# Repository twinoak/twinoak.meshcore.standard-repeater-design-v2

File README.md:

# TwinOak Standard Repeater Design v2

## General design concept and project goals
The thought behind this project came to life after quite a few failures in OTA firmware updates. There was need for a better, and more stable, way of doing the firmware updates. 
Besides the devices being bricked from the OTA process, repeaters can also sit quite a long distance away, so it would also be desireable to have something that could update remotely, from the comfort of a desk. 
One could consider using LoRa for sending the updates to the repeaters, but since the network is already congested enough, it seems like a bad idea to pile even more load on that band, even assuming that it somehow would be possible to get a stable link to all the repeater sites.

It was decided to go for a design which incorporated an LTE-M module for managinge the node. This gives almost 100% coverage(in Denmark at least!) and high bandwidth for firmware transfers. 
The structure looked something like this:
```mermaid
flowchart LR
    subgraph Mesh plane
    A@{ shape: cloud, label: "Mesh network" } <--> B[LoRa module]
    end
    B[LoRa module] <-.-> C[LTE-M module]
    subgraph Management plane
    C <--> D@{ shape: cloud, label: "Internet" }
    end
```

Besides the problematic management of remote nodes, there is also a few other features to address with this new repeater design. This meant that the primary goals for the project ended up being:
1. <b>Remote management</b>. Being able to do management remotely based on existing LTE infrastructure. Only management, no data via LTE.
2. <b>Superior noise "rejection"</b> with radio in RF shielding and using proper cables and isolation to give the LoRa the best possible noise floor. Previous experience with SenseCAP Solar P1 nodes, even though they are very nice nodes, proved that they are just plastic enclosures with no RF protection. Put them next to a cell tower and you are in trouble! A bit ironic that the biggest nemesis regarding noise in MeshCore repeaters is LTE, when this going to use LTE as the transport for the management plane!
3. <b>Integrated cavity filter</b>. There has been multiple issues with noise in all many locations. There is always a cell tower(or some DAB/DVT/whatever tower) sitting just next to great locations. The Solar P1 only offers the option to add a small SAW filter, but one goal of this project is that it should to be easy to add a good cavity filter. Even maybe be the default.
4. <b>Modularity</b>. Things change fast; firmware, features and other software changes fast! But hardware also changes. With the Solar P1 one would have to replace the entire unit if a new and better radio became available. This project should solve this by enabling changing JUST the radio or JUST the solarpanel or JUST the batteries. Not doing a complete "forklift upgrade" everytime is a must.

## Hardware design principle
The hardware is split into 3 parts:
1. The LoRa part
2. The power part
3. The management part

To make these function together in a modular way each part has been split into multiple "levels" with increasing amount of specialization the higher the level. This has been illustrated here:
```mermaid
block
  columns 7
  block:stuff:2
    columns 1
    A1["LoRa modul"] 
    space
    A2["LoRa adapter board"] 
    space
    A3["Platform board"]
    space
    space
  end
  space
  block:stuff2:2
    columns 1
    space
    space
    space
    space
    B3["Platform mgmt"]
    space
    B4["Power"]
  end
  space
  block:stuff3:2
    columns 1
    C1["LTE modul"] 
    space
    C2["LTE adapter board"]
    space
    C3["Platform board"]
    space
    space
  end

  %% Arrows vertically
  A1 <--> A2
  A2 <--> A3

  B4 --> B3

  C1 <--> C2
  C2 <--> C3

  %% Arrows horisontally
  A3 <--> B3
  B3 <--> C3
```
From the bottom up:
- <b>Power</b> is just that: Simple DC power source from either solarpanel, grid connection or battery.
- <b>Platform</b> and <b>Platform management</b> is introducing management of the power from the power source and handling signaling between the two platform boards. Each platformboard is just supplying simple power to the upper levels and generic IO between the levels.
- <b>Adapters</b> change the generic IO and power from the platform to the specific needs of the module above it. That could be board specific power management, levelshifting of IO signals and routing to the proper pins for the given module above.
- <b>Radio modules</b> is the actual off-the-shelf radio modules, such as a Heltec LoRa module like the T096 or similar.

Each of the 3 parts should be kept as RF isolated as possible as the two radio modules will likely interfer with each other. So the parts also indicate an "physical seperation" with RF shielding. To make this as good as possible the entire repeater should be house inside a RF shielded enclosure and both the LoRa part and the management part should be kept in seperate RF shielded enclosures. Great care should be taken at the interfaces between each part, such that RF noise don't traverse the bounderies between each part.

### Pinouts and inter-board wiring

Every pin of the D-subs, the A↔B ribbon, the platform boards and all adapter mappings is documented in
[`hardware/pcb/INTERCONNECT.md`](hardware/pcb/INTERCONNECT.md) — including the I2C bus plan (LoRa is master,
INA3221 @0x42, RV-3028 @0x52), the LoRa↔Walter UART link, the remote power-kill behaviour and JLCPCB part
references. Update that file first whenever the wiring changes.

## Bill-of-materials and links to sources

| Component            | Brand      | Model                             | Source                                                                                                   | Price     |
|----------------------|------------|-----------------------------------|----------------------------------------------------------------------------------------------------------|----------:|
| <u>*External components*</u>                                                                                                                                                                 |
| Antenna, LoRa        | Vinnant    | CC868/8-PEL 10dBi                 | [Hoeg teknik](https://hoegteknik.dk/shop/da/dv-nodermeshtastic/483-8dbd-58-antenne-for-868-mhz.html)     |   599 DKK |
| Antenna, LTE-M       | SR passives| IP67, N-Male, 5dBi                | [TME](https://www.tme.eu/dk/en/details/5g-ant-rs02w-n/gsm-antennas/sr-passives/)                         |    73 DKK |
| Cable                | Bevotop    | LMR240, N Male to N Male, 80cm    | [Aliexpress](https://www.aliexpress.com/item/1005002640557645.html)                                      |   ~70 DKK |
| Pipe                 |            | 1" pipe, 200cm                    | [Webshop](https://shop.erik-larsen.dk/products/pipe-galv?variant=39625182412883)                         |   150 DKK |
| Brackets             |            | Pipeclamps, set of 2, max 60mm    | [Amazon](https://www.amazon.de/-/da/Premium-mastklemme-dobbeltklemme-galvaniseret-dobbelt/dp/B010UL5B66) |   ~67 DKK |
| Enclosure            |            | Diecast alu box, IP67             | [Aliexpress](https://www.aliexpress.com/item/1005007492347455.html)                                      |  ~185 DKK |
| Solar panel          | Cellevia   | 10W Solar Panel                   | [TME](https://www.tme.eu/dk/en/details/cl-sm10p/photovoltaic-modules/cellevia-power/)                    |    76 DKK |
| Vent valve           |            | M16 watertight alu vent valve     | [Aliexpress](https://www.aliexpress.com/item/1005012242062756.html)                                      |   ~20 DKK |
| Bracket              |            | For solar panel                   | TBD                                                                                                      |           |
| Bracket              |            | For enclosure                     | TBD                                                                                                      |           |
| <u>*Internal components*</u>                                                                                                                                                                 |
| Backplates           | Custom     | Set of 2pce, 1,5mm lasercut alu   | (Fusion link? DXF?)                                                                                      |   280 DKK |
| RF boxes             | Gainta     | G103-IP67, 64x98x34mm, alu, 2pce  | [TME](https://www.tme.eu/dk/en/details/g103-ip67/multipurpose-enclosures/gainta/)                        |   108 DKK |
| Cavity filter        | Sysmocom   | 7Mhz Cavity filter(Link to test?) | [Sysmocom](https://shop.sysmocom.de/868-863..870-MHz-cavity-filter-ISM-LoRa-SigFox-Helium/cf866.5-kt30)  |  ~400 DKK |
| Battery              | Meshnology | 10.000mA LiPo battery             | [Meshnology](https://meshnology.com/collections/frontpage/products/3-7v-10000mah-lipo-battery-with-usb-charger-protection-for-arduino-esp32-drone?variant=46431266963694) | ~150 DKK |
| Battery NTC          | muRata     | NXFT15XH103FEAB050, 10k ±1%, B25/85 3434K, 50 mm leads — must be a B≈3435K part (TS divider R5/R6 on conn-B); a generic B3950 NTC moves the charge window to 3.5…38.6 °C | [LCSC C17314387](https://www.lcsc.com/product-detail/C17314387.html) | ~4 DKK |
| Connector, NTC (J6)  | JST        | PHR-2 housing + 2x SPH-002T-P0.5S contact (24–30 AWG), JST PH 2.0 mm | [LCSC C157955](https://www.lcsc.com/product-detail/C157955.html) / [C111515](https://www.lcsc.com/product-detail/C111515.html) | <1 DKK |
| Connector, battery (J7) | JST     | EHR-2 housing + 2x SEH-001T-P0.6L contact (22–26 AWG, use 22 AWG for the 2 A lead; P0.6 C263767 covers 22–30), JST EH 2.5 mm | [LCSC C161659](https://www.lcsc.com/product-detail/C161659.html) / [C392073](https://www.lcsc.com/product-detail/C392073.html) | <1 DKK |
| Cable                |            | U.FL -> SMA pigtail, 10cm         | [Aliexpress](https://www.aliexpress.com/item/1005009937311685.html)                                      |   ~10 DKK |
| Cable                |            | N-female -> SMA pigtail, 10cm     | [Aliexpress](https://www.aliexpress.com/item/1005008984322302.html)                                      |   ~10 DKK |
| Cable                |            | N-female -> SMA pigtail, 20cm     | [Aliexpress](https://www.aliexpress.com/item/1005008984322302.html)                                      |   ~10 DKK |
| Cable                |            | SMA -> SMA pigtail, 10cm          | [Aliexpress](https://www.aliexpress.com/item/1005006890065800.html)                                      |   ~10 DKK |
| <u>*Radio modules*</u>                                                                                                                                                                       |
| LoRa module          | Heltec     | Heltec V3, ESP32 based            | [Heltec](https://heltec.org/project/wifi-lora-32-v3/)                                                    |  ~120 DKK |
| *...or...*                                                                                                                                                                                   |
| LoRa module          | Heltec     | Heltec T096, nRF52 based          | [Heltec](https://heltec.org/project/t096/)                                                               |  ~230 DKK |
| LTE module           | Quickspot  | Walter LTE MCU, ESP32 based       | [TinyTronics](https://www.tinytronics.nl/nl/development-boards/microcontroller-boards/met-telecommunicatie/walter-esp32-s3-iot-development-board-cat-m-nb-iot-en-gnss-gm02sp) |   ~510 DKK |
| <u>*Custom PCBs*</u>                                                                                                                                                                         |
| Platform board       |            | TBD                               |                                                                                                          |           |
| Heltec V3 adapter    |            | TBD                               |                                                                                                          |           |
| *...or...*                                                                                                                                                                                   |
| Heltec T096 adapter  |            | TBD                               |                                                                                                          |           |
| LoRa connector board |            | TBD                               |                                                                                                          |           |
| LTE connector board  |            | TBD                               |                                                                                                          |           |
| <u>*Electrical components*</u>                                                                                                                                                               |
| D-sub connector      | Amphenol   | FCE17-E09SM-250, 9-pin, filter, x2| [Mouser](https://eu.mouser.com/en/ProductDetail/Amphenol-Commercial-Products/FCE17-E09SM-250)            |  ~175 DKK |
| D-sub connector      | Amphenol   | L717DFE09PT, 9-pin, male PCB, x2  | [Mouser](https://eu.mouser.com/en/ProductDetail/Amphenol-Commercial-Products/L717DFE09PT)                |  ~100 DKK |
| Capacitor            | Panasonic  | 16SEPG470M, 470µF PolyAlu, x1 — or JLC-assemblable Honor Elec RYHT16V470UF8*11 (LCSC C48970577, 8×11.5 mm, 3.5 mm pitch, 14 mΩ, 125 °C) | [TME](https://www.tme.eu/dk/en/details/16sepg470m/tht-polymer-capacitors/panasonic/) / [JLCPCB](https://jlcpcb.com/partdetail/C48970577) |   ~10 DKK |
| Capacitor            | AISHI      | EWH1CM101E11OT, 100µF, x2         | [TME](https://www.tme.eu/dk/en/details/ce-100_16pht-y/tht-electrolytic-capacitors/aishi/ewh1cm101e11ot/) |    ~1 DKK |
| Capacitor            | SR passives| CCT-10N/100V-S, 10nF Ceramic, x2  | [TME](https://www.tme.eu/dk/en/details/cct-10n_100v-s/mlcc-tht-capacitors/sr-passives/ct40805b103k101f1r/) |  ~1 DKK |                                                                                                        |           |
| Connector            |            | Pin headers for radio modules?    | TBD                                                                                                      |           |
| Connector            |            | Low profile headers for adapters? | TBD                                                                                                      |           |

Total: ~3.250DKK + TBD + solder/heatshrink/screws/wires/etc + shipping/customs/fees/etc

## LTE-M providers

### Lebara
Lebara SIM card, their cheapest plan, has been tested and it worked fine with the Walter MCU and could get contact with the internet without issues.

### NexCon
The LTE provider nexcon.io has been tested. They have a 25MB/month plan that is VERY cheap, like 1eur/month per SIM card including a management website that is VERY nice! Can highly recommend them, however they might only serve commercial customers, so check that first.

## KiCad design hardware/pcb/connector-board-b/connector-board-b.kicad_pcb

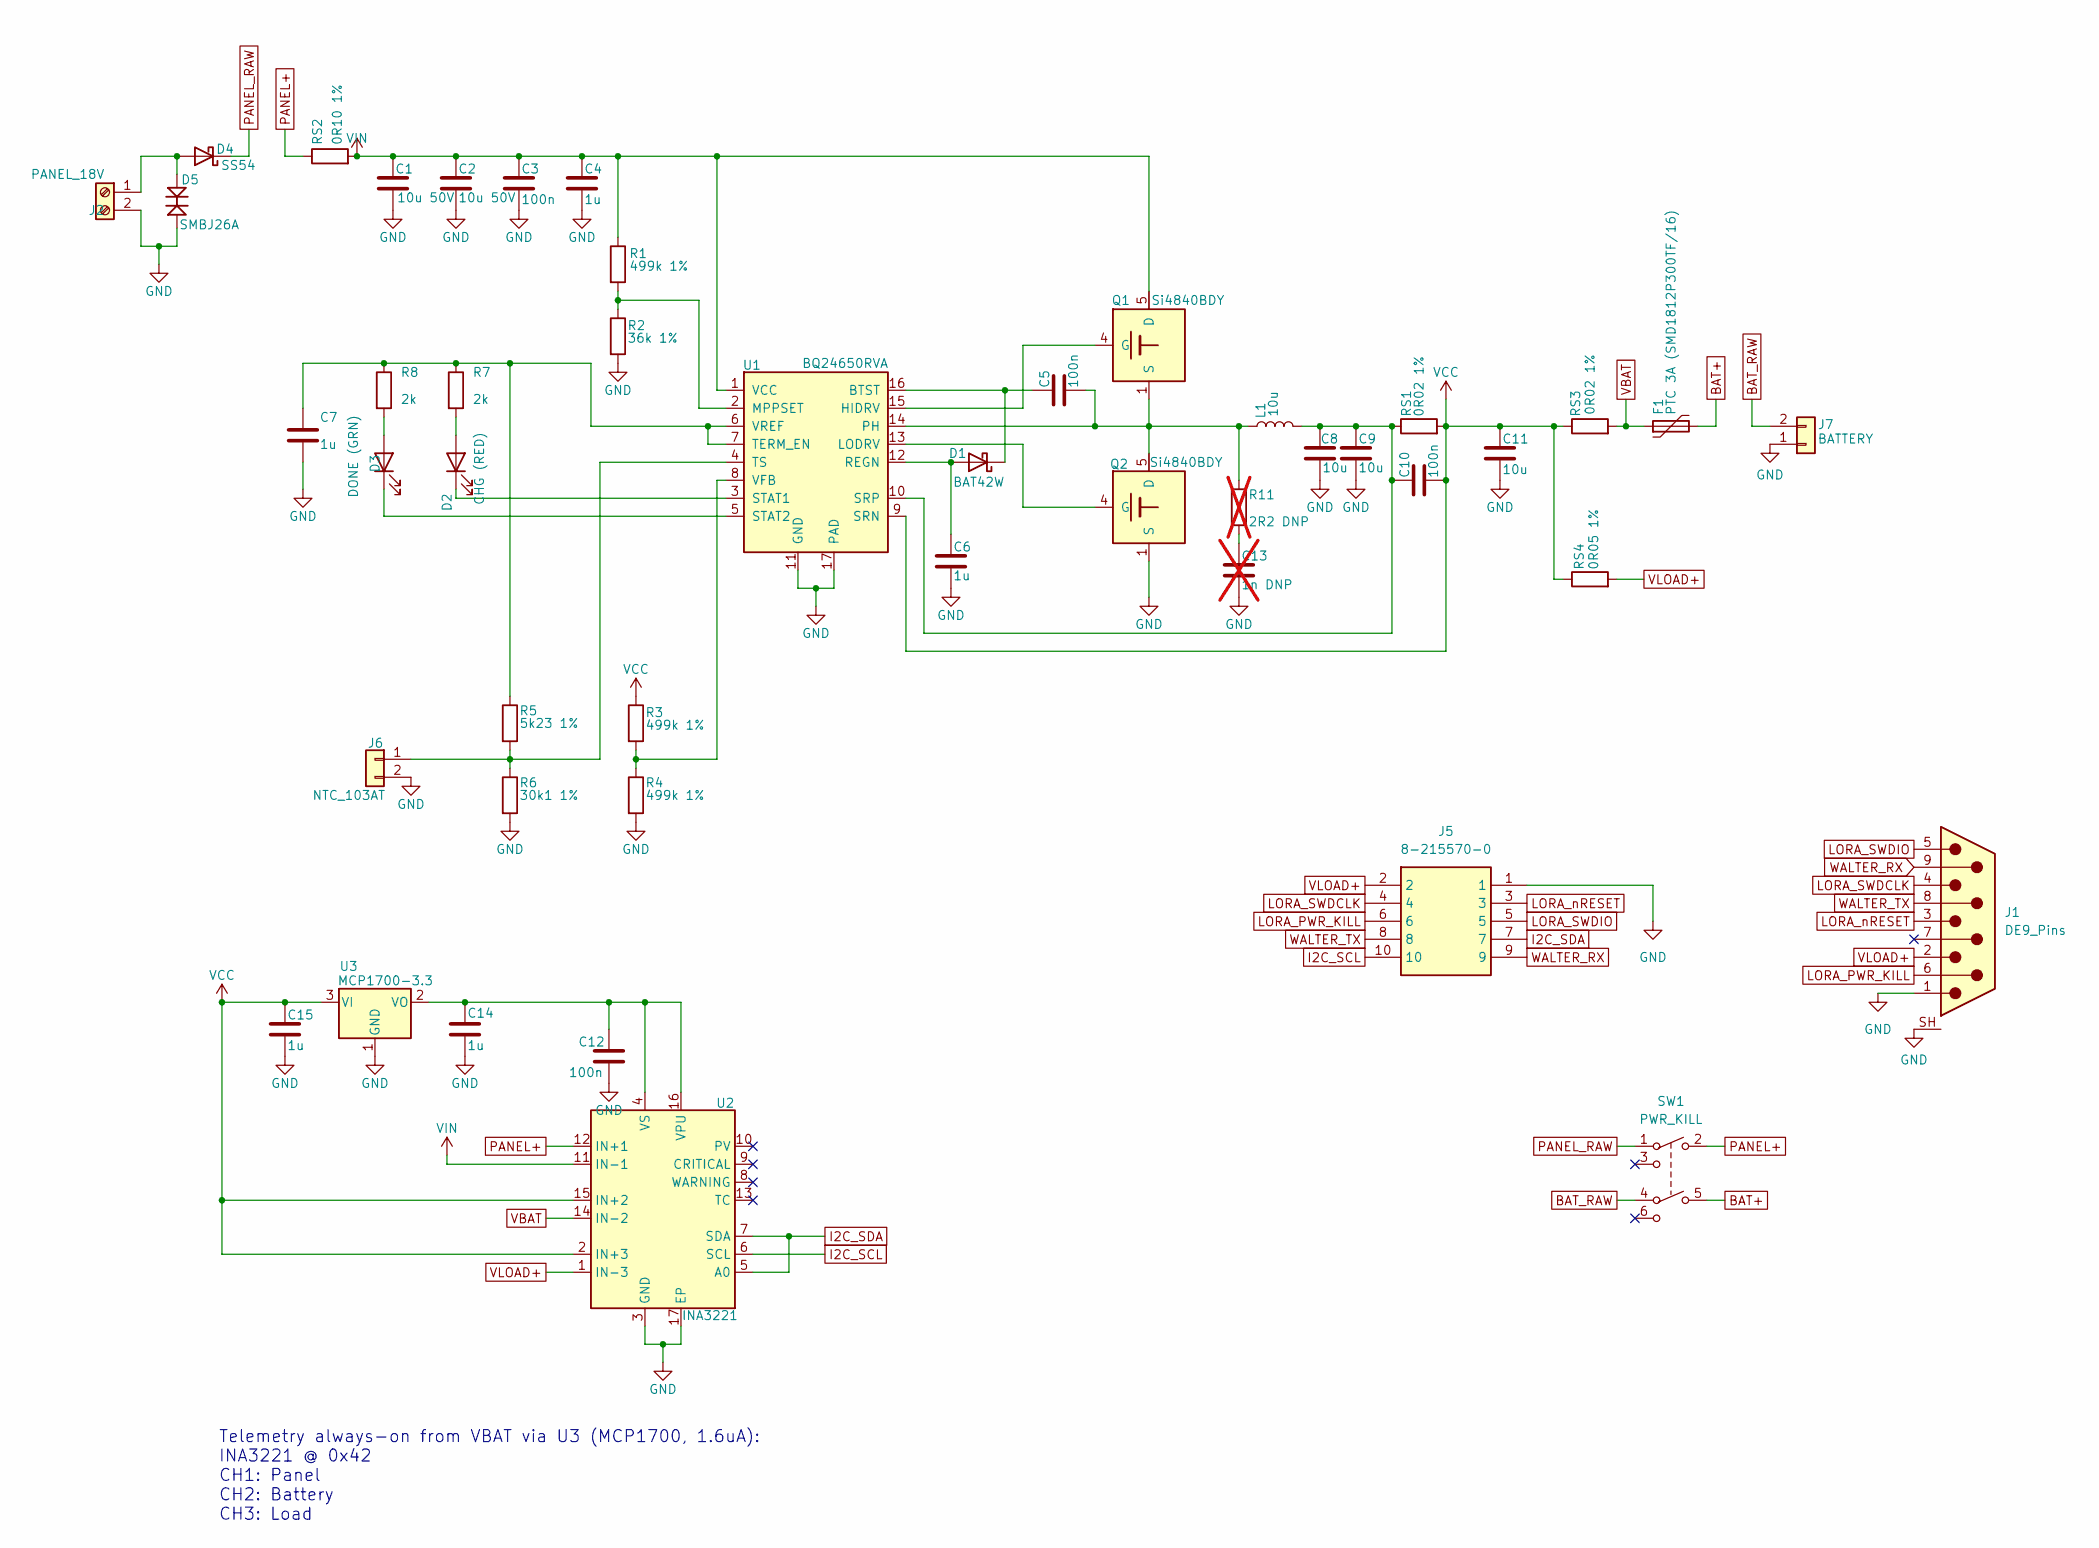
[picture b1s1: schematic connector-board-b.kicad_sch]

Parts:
C1, C2: 10u 50V; C_1210_3225Metric; LCSC Part # C138687
C3, C5, C10, C12: 100n; C_0805_2012Metric; LCSC Part # C49678
C4, C6, C7, C14, C15: 1u; C_0805_2012Metric; LCSC Part # C28323
C8, C9, C11: 10u; C_1206_3216Metric; LCSC Part # C13585
C13: 1n DNP; C_0805_2012Metric; LCSC Part # C94121; not fitted
D1: BAT42W; D_SOD-123; LCSC Part # C134396
D2: CHG (RED); LED_0805_2012Metric; LCSC Part # C84256
D3: DONE (GRN); LED_0805_2012Metric; LCSC Part # C2297
D4: SS54; D_SMA; LCSC Part # C22452
D5: SMBJ26A; D_SMB; LCSC Part # C123820
F1: PTC 3A (SMD1812P300TF/16); Fuse_1812_4532Metric; LCSC Part # C702820
J1: DE9_Pins; DSUB-9_Pins_Vertical_P2.77x2.84mm_MountingHoles
J2: PANEL_18V; TerminalBlock_MaiXu_MX126-5.0-02P_1x02_P5.00mm; LCSC Part # C5188434
J5: 8-215570-0; 82155700; Manufacturer_Part_Number 8-215570-0
J6: NTC_103AT; JST_PH_B2B-PH-K_1x02_P2.00mm_Vertical; LCSC Part # C131337
J7: BATTERY; JST_EH_B2B-EH-A_1x02_P2.50mm_Vertical; LCSC Part # C160262
L1: 10u; L_Vishay_IHLP-4040; LCSC Part # C845066
Q1, Q2: Si4840BDY; SOIC-8_3.9x4.9mm_P1.27mm; LCSC Part # C558269
R1, R3, R4: 499k 1%; R_0805_2012Metric; LCSC Part # C17721
R2: 36k 1%; R_0805_2012Metric; LCSC Part # C4360
R5: 5k23 1%; R_0805_2012Metric; LCSC Part # C17739
R6: 30k1 1%; R_0805_2012Metric; LCSC Part # C21841
R7, R8: 2k; R_0805_2012Metric; LCSC Part # C17604
R11: 2R2 DNP; R_0805_2012Metric; not fitted
RS1, RS3: 0R02 1%; R_1206_3216Metric; LCSC Part # C2903502
RS2: 0R10 1%; R_1206_3216Metric; LCSC Part # C25334
RS4: 0R05 1%; R_1206_3216Metric; LCSC Part # C2904224
SW1: PWR_KILL; SW_Toggle_CAX_MTS202C3D1_RightAngle; LCSC Part # C55159901
U1: BQ24650RVA; Texas_RVA0016A_VQFN-16-1EP_3.5x3.5mm_P0.5mm_EP2.1x2.1mm; LCSC Part # C53712
U2: INA3221; Texas_RGV0016A_VQFN-16-1EP_4x4mm_P0.65mm_EP2.1x2.1mm; LCSC Part # C181255
U3: MCP1700-3.3; SOT-23; LCSC Part # C39051

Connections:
BAT+: F1.2, SW1.5 (COM2)
BAT_RAW: J7.2, SW1.4 (A2)
GND: C1.2, C2.2, C3.2, C4.2, C6.2, C7.2, C8.2, C9.2, C11.2, C12.2, C13.2, C14.2, C15.2, D5.2, J1.1 (1_1), J1.SH, J2.2, J5.1, J6.2, J7.1, Q2.1 (S), Q2.2 (S), Q2.3 (S), R2.2, R4.2, R6.2, U1.11 (GND), U1.17 (PAD), U2.3 (GND), U2.17 (EP), U3.1 (GND)
I2C_SCL: J5.10, U2.6 (SCL)
I2C_SDA: J5.7, U2.5 (A0), U2.7 (SDA)
LORA_PWR_KILL: J1.6 (6_6), J5.6
LORA_SWDCLK: J1.4 (4_4), J5.4
LORA_SWDIO: J1.5 (5_5), J5.5
LORA_nRESET: J1.3 (3_3), J5.3
unnamed: C13.1, R11.2
unnamed: C6.1, D1.2 (A), U1.12 (REGN)
unnamed: C5.1, D1.1 (K), U1.16 (BTST)
unnamed: D2.2 (A), R7.2
unnamed: D2.1 (K), U1.3 (STAT1)
unnamed: D3.2 (A), R8.2
unnamed: D3.1 (K), U1.5 (STAT2)
unnamed: D4.2 (A), D5.1, J2.1
unnamed: J6.1, R5.2, R6.1, U1.4 (TS)
unnamed: Q1.4 (G), U1.15 (HIDRV)
unnamed: Q2.4 (G), U1.13 (LODRV)
unnamed: R1.2, R2.1, U1.2 (MPPSET)
unnamed: C5.2, L1.1, Q1.1 (S), Q1.2 (S), Q1.3 (S), Q2.5 (D), Q2.6 (D), Q2.7 (D), Q2.8 (D), R11.1, U1.14 (PH)
unnamed: C8.1, C9.1, C10.1, L1.2, RS1.1, U1.10 (SRP)
unnamed: C7.1, R5.1, R7.1, R8.1, U1.6 (VREF), U1.7 (TERM_EN)
unnamed: R3.2, R4.1, U1.8 (VFB)
unnamed: C12.1, C14.1, U2.4 (VS), U2.16 (VPU), U3.2 (VO)
PANEL+: RS2.1, SW1.2 (COM1), U2.12 (IN+1)
PANEL_RAW: D4.1 (K), SW1.1 (A1)
VBAT: F1.1, RS3.2, U2.14 (IN-2)
VCC: C10.2, C11.1, C15.1, R3.1, RS1.2, RS3.1, RS4.1, U1.9 (SRN), U2.2 (IN+3), U2.15 (IN+2), U3.3 (VI)
VIN: C1.1, C2.1, C3.1, C4.1, Q1.5 (D), Q1.6 (D), Q1.7 (D), Q1.8 (D), R1.1, RS2.2, U1.1 (VCC), U2.11 (IN-1)
VLOAD+: J1.2 (2_2), J5.2, RS4.2, U2.1 (IN-3)
WALTER_RX: J1.9 (9_9), J5.9
WALTER_TX: J1.8 (8_8), J5.8

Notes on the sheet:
Telemetry always-on from VBAT via U3 (MCP1700, 1.6uA): INA3221 @ 0x42 CH1: Panel CH2: Battery CH3: Load

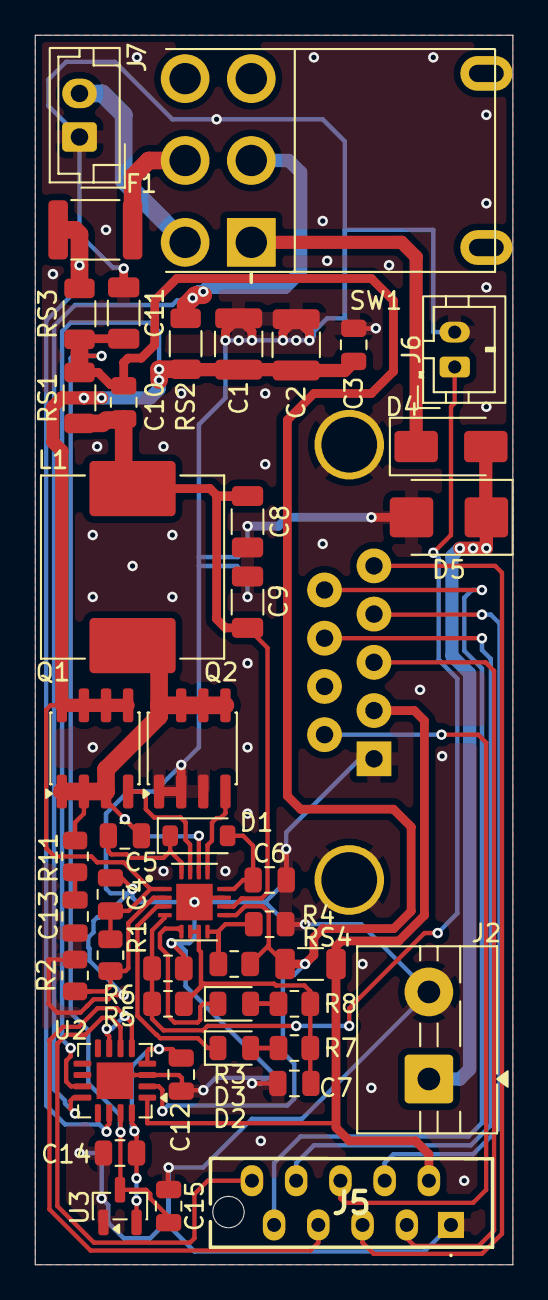
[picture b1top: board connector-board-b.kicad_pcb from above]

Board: 2 copper layers, 27.4 x 70.6 mm, 46 parts (1 on the bottom side), 34 nets.

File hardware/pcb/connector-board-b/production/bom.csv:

Designator,Footprint,Quantity,Value,LCSC Part #
"C1, C2",1210,2,10u 50V,C138687
"C10, C12, C3, C5",0805,4,100n,C49678
"C11, C8, C9",1206,3,10u,C13585
"C14, C15, C4, C6, C7",0805,5,1u,C28323
D1,D_SOD-123,1,BAT42W,C134396
D2,0805,1,CHG (RED),C84256
D3,0805,1,DONE (GRN),C2297
D4,D_SMA,1,SS54,C22452
D5,D_SMB,1,SMBJ26A,C123820
F1,1812,1,PTC 3A (SMD1812P300TF/16),C702820
L1,L_Vishay_IHLP-4040,1,10u,C845066
"Q1, Q2",SOIC-8_3.9x4.9mm_P1.27mm,2,Si4840BDY,C558269
"R1, R3, R4",0805,3,499k 1%,C17721
R2,0805,1,36k 1%,C4360
R5,0805,1,5k23 1%,C17739
R6,0805,1,30k1 1%,C21841
"R7, R8",0805,2,2k,C17604
"RS1, RS3",1206,2,0R02 1%,C2903502
RS2,1206,1,0R10 1%,C25334
RS4,1206,1,0R05 1%,C2904224
U1,Texas_RVA0016A_VQFN-16-1EP_3.5x3.5mm_P0.5mm_EP2.1x2.1mm,1,BQ24650RVA,C53712
U2,Texas_RGV0016A_VQFN-16-1EP_4x4mm_P0.65mm_EP2.1x2.1mm,1,INA3221,C181255
U3,SOT-23,1,MCP1700-3.3,C39051

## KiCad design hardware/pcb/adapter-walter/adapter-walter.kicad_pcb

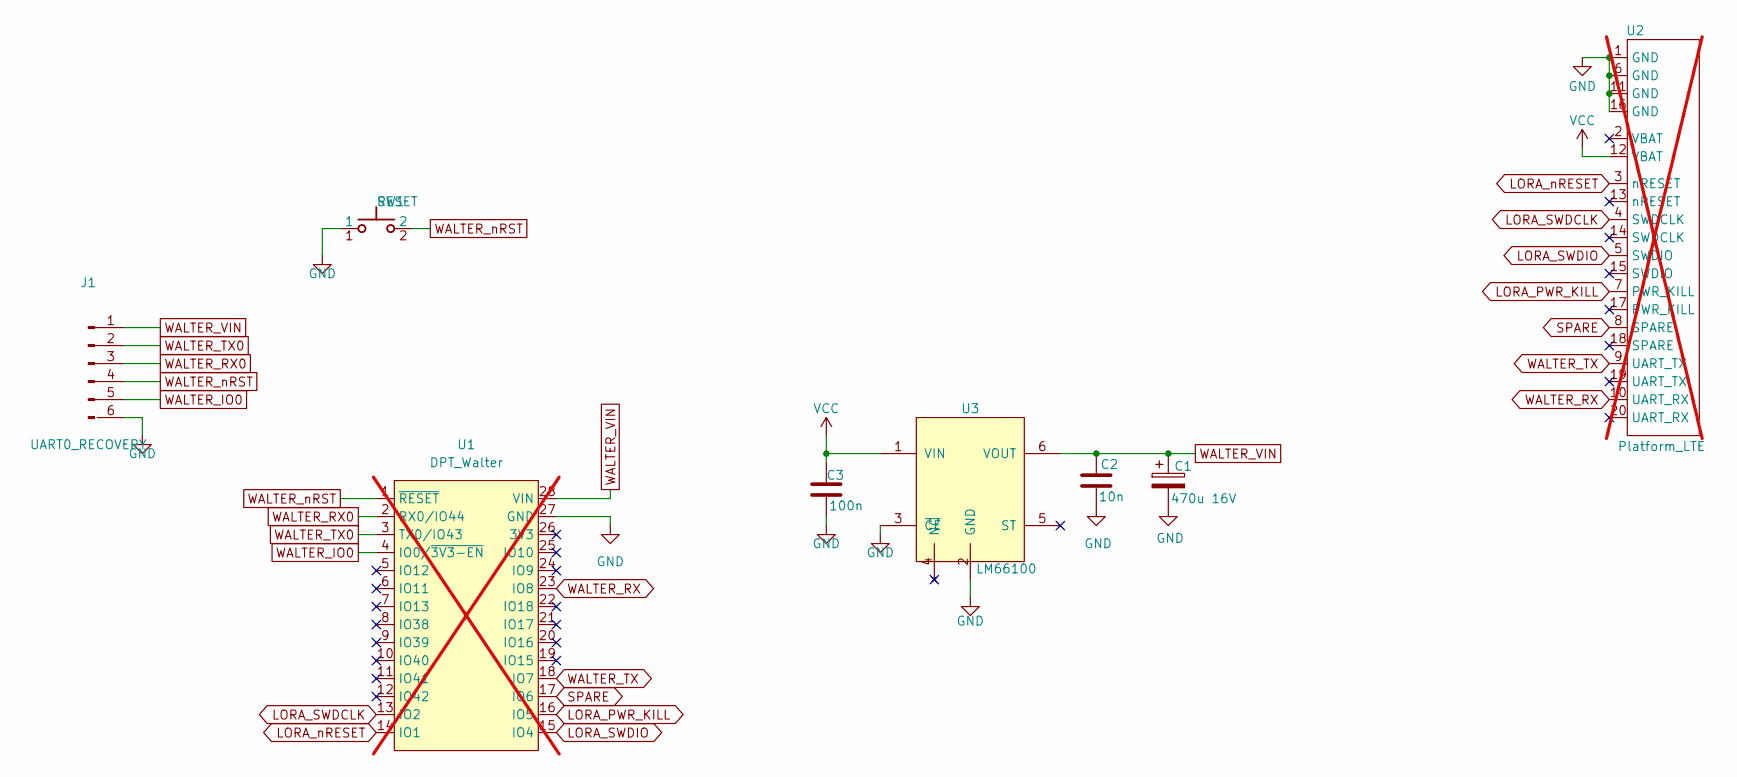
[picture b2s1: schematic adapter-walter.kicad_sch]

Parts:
C1: 470u 16V; CP_Radial_D8.0mm_P3.50mm; MPN Honor Elec RYHT16V470UF8*11 (alt. Panas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; LCSC Part # C48970577
C2: 10n; C_Rect_L4.0mm_W2.5mm_P2.50mm; MPN SR Passives CCT-10N/100V-S
C3: 100n; C_0805_2012Metric_Pad1.18x1.45mm_HandSolder; LCSC Part # C49678
J1: UART0_RECOVERY; PinHeader_1x06_P2.54mm_Vertical
SW1: RESET; SW_Push_Kinghelm_KH-6X6X5H-STM; LCSC Part # C2837531
U1: DPT_Walter; walter-socket; not fitted
U2: Platform_LTE; platform-adapter-footprint; not fitted
U3: LM66100; SOT-363_SC-70-6; LCSC Part # C2832141

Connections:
GND: C1.2, C2.2, C3.2, J1.6, SW1.1, U1.27 (GND), U2.1 (GND), U2.6 (GND), U2.11 (GND), U2.16 (GND), U3.2 (GND), U3.3 (~CE)
LORA_PWR_KILL: U1.16 (IO5), U2.7 (PWR_KILL)
LORA_SWDCLK: U1.13 (IO2), U2.4 (SWDCLK)
LORA_SWDIO: U1.15 (IO4), U2.5 (SWDIO)
LORA_nRESET: U1.14 (IO1), U2.3 (nRESET)
SPARE: U1.17 (IO6), U2.8 (SPARE)
VCC: C3.1, U2.12 (VBAT), U3.1 (VIN)
WALTER_IO0: J1.5, U1.4 (IO0/~3V3-EN)
WALTER_RX: U1.23 (IO8), U2.10 (UART_RX)
WALTER_RX0: J1.3, U1.2 (RX0/IO44)
WALTER_TX: U1.18 (IO7), U2.9 (UART_TX)
WALTER_TX0: J1.2, U1.3 (TX0/IO43)
WALTER_VIN: C1.1, C2.1, J1.1, U1.28 (VIN), U3.6 (VOUT)
WALTER_nRST: J1.4, SW1.2, U1.1 (~RESET)

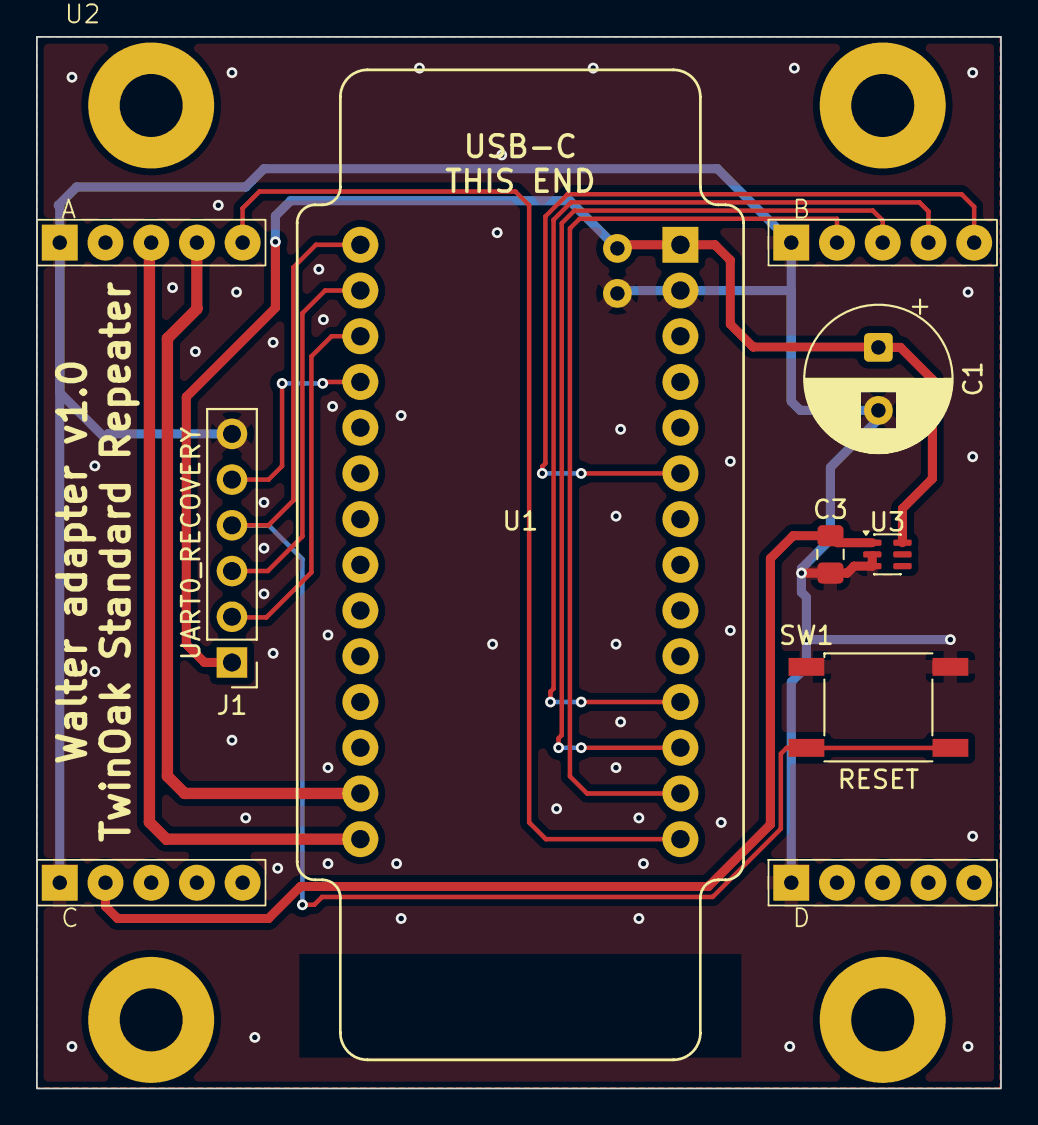
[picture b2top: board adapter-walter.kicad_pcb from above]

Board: 2 copper layers, 53.6 x 58.4 mm, 8 parts (1 on the bottom side), 14 nets.

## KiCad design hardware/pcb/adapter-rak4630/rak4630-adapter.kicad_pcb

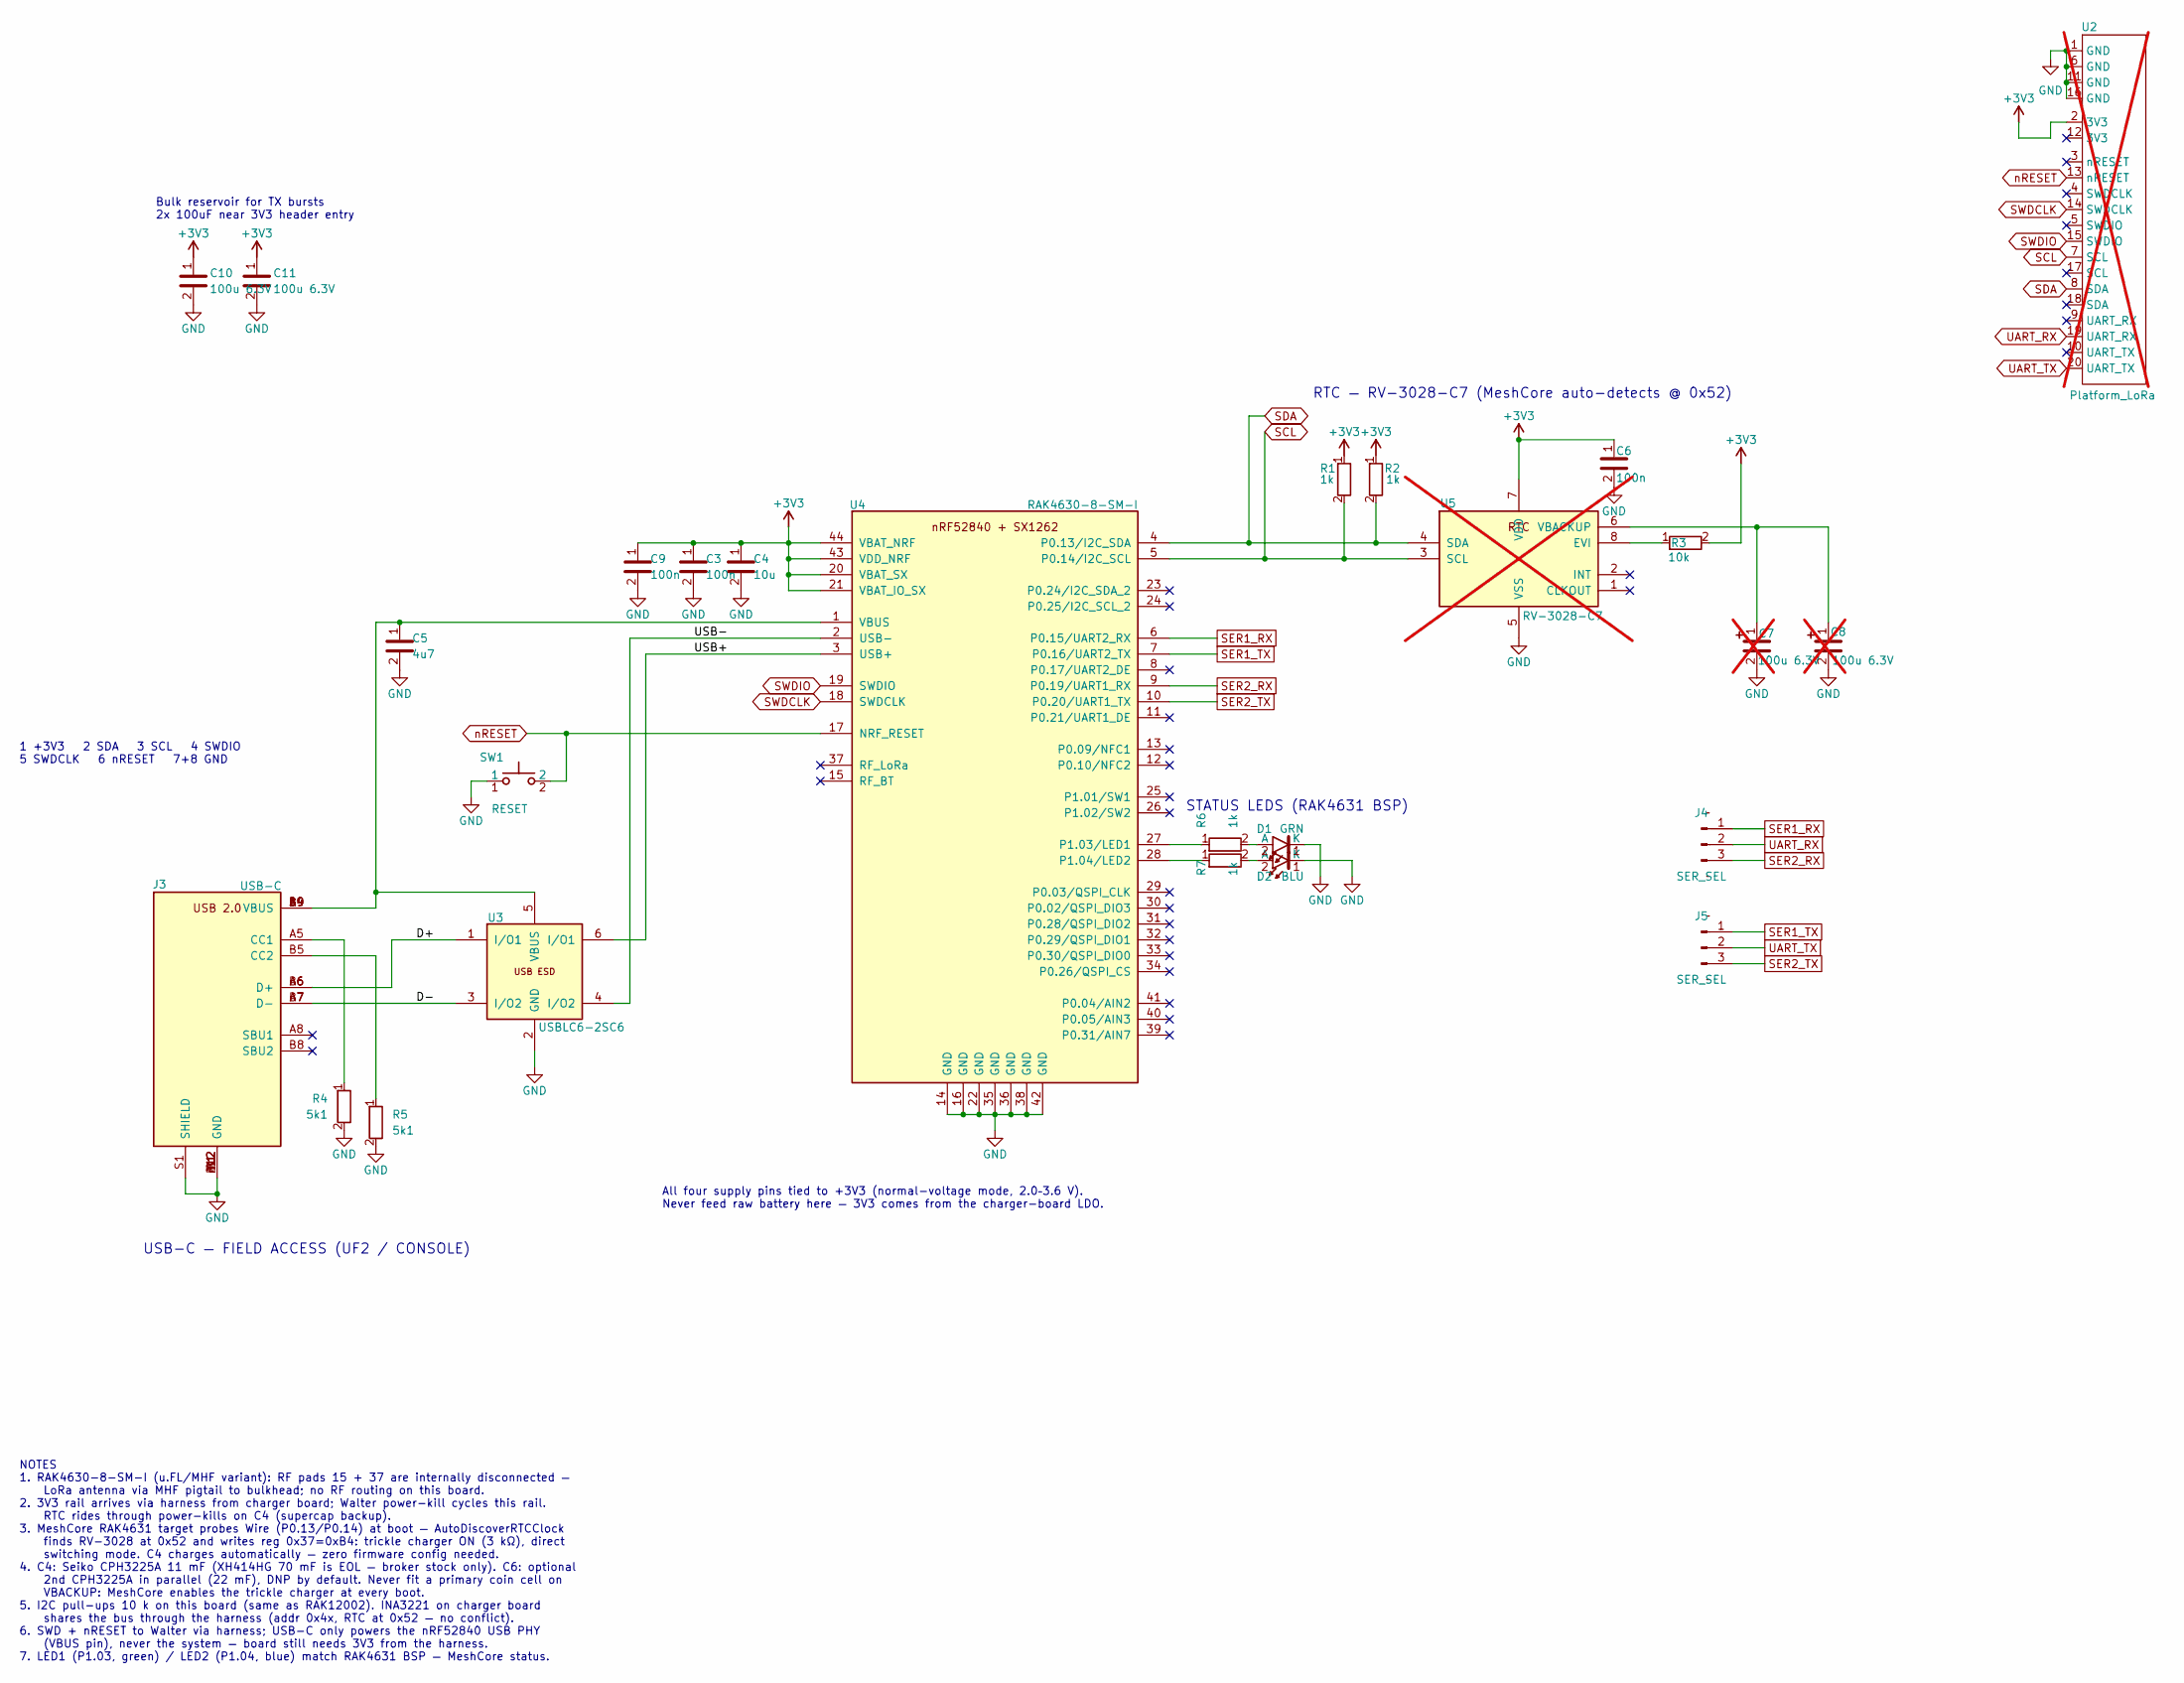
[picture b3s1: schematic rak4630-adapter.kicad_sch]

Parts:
C3, C6, C9: 100n; C_0805_2012Metric_Pad1.18x1.45mm_HandSolder; LCSC Part # C49678
C4: 10u; C_0805_2012Metric_Pad1.18x1.45mm_HandSolder; LCSC Part # C15850
C5: 4u7; C_0805_2012Metric_Pad1.18x1.45mm_HandSolder; LCSC Part # C1779
C7, C8: 100u 6.3V; CPH3225A; LCSC Part # C49066; not fitted
C10, C11: 100u 6.3V; CPH3225A; LCSC Part # C49066
D1: GRN; LED_0805_2012Metric; LCSC Part # C2297
D2: BLU; LED_0805_2012Metric; LCSC Part # C2293
J3: USB-C; USB_C_Receptacle_XUNPU_TYPEC-303-ACP16_Vertical; LCSC Part # C720628
J4, J5: SER_SEL; PinHeader_1x03_P2.54mm_Vertical
R1, R2, R6, R7: 1k; R_0805_2012Metric_Pad1.20x1.40mm_HandSolder; LCSC Part # C17513
R3: 10k; R_0805_2012Metric_Pad1.20x1.40mm_HandSolder; LCSC Part # C17414
R4, R5: 5k1; R_0805_2012Metric_Pad1.20x1.40mm_HandSolder; LCSC Part # C27834
SW1: RESET; SW_Push_Kinghelm_KH-6X6X5H-STM; LCSC Part # C2837531
U2: Platform_LoRa; platform-adapter-footprint; not fitted
U3: USBLC6-2SC6; SOT-23-6; LCSC Part # C7519
U4: RAK4630-8-SM-I; RAK4630; LCSC Part # C32315253
U5: RV-3028-C7; LCSC Part # C3304278; not fitted

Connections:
+3V3: C3.1, C4.1, C6.1, C9.1, C10.1, C11.1, R1.1, R2.1, R3.2, U2.2 (3V3), U4.20 (VBAT_SX), U4.21 (VBAT_IO_SX), U4.43 (VDD_NRF), U4.44 (VBAT_NRF), U5.7 (VDD)
/D+: J3.A6 (D+), J3.B6 (D+), U3.1 (I/O1)
/D-: J3.A7 (D-), J3.B7 (D-), U3.3 (I/O2)
/USB+: U3.6 (I/O1), U4.3 (USB+)
/USB-: U3.4 (I/O2), U4.2 (USB-)
GND: C3.2, C4.2, C5.2, C6.2, C7.2, C8.2, C9.2, C10.2, C11.2, D1.1 (K), D2.1 (K), J3.A1 (GND), J3.A12 (GND), J3.B1 (GND), J3.B12 (GND), J3.S1 (SHIELD), R4.2, R5.2, SW1.1, U2.1 (GND), U2.6 (GND), U2.11 (GND), U2.16 (GND), U3.2 (GND), U4.14 (GND), U4.16 (GND), U4.22 (GND), U4.35 (GND), U4.36 (GND), U4.38 (GND), U4.42 (GND), U5.5 (VSS)
unnamed: D1.2 (A), R6.2
unnamed: D2.2 (A), R7.2
unnamed: J3.A5 (CC1), R4.1
unnamed: J3.B5 (CC2), R5.1
unnamed: C5.1, J3.A4 (VBUS), J3.A9 (VBUS), J3.B4 (VBUS), J3.B9 (VBUS), U3.5 (VBUS), U4.1 (VBUS)
unnamed: R6.1, U4.27 (P1.03/LED1)
unnamed: R7.1, U4.28 (P1.04/LED2)
unnamed: R3.1, U5.8 (EVI)
unnamed: C7.1, C8.1, U5.6 (VBACKUP)
SCL: R1.2, U2.7 (SCL), U4.5 (P0.14/I2C_SCL), U5.3 (SCL)
SDA: R2.2, U2.8 (SDA), U4.4 (P0.13/I2C_SDA), U5.4 (SDA)
SER1_RX: J4.1, U4.6 (P0.15/UART2_RX)
SER1_TX: J5.1, U4.7 (P0.16/UART2_TX)
SER2_RX: J4.3, U4.9 (P0.19/UART1_RX)
SER2_TX: J5.3, U4.10 (P0.20/UART1_TX)
SWDCLK: U2.14 (SWDCLK), U4.18 (SWDCLK)
SWDIO: U2.15 (SWDIO), U4.19 (SWDIO)
UART_RX: J4.2, U2.19 (UART_RX)
UART_TX: J5.2, U2.20 (UART_TX)
nRESET: SW1.2, U2.13 (nRESET), U4.17 (NRF_RESET)

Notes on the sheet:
Bulk reservoir for TX bursts 2x 100uF near 3V3 header entry
1 +3V3 2 SDA 3 SCL 4 SWDIO 5 SWDCLK 6 nRESET 7+8 GND
USB-C — FIELD ACCESS (UF2 / CONSOLE)
STATUS LEDS (RAK4631 BSP)
RTC — RV-3028-C7 (MeshCore auto-detects @ 0x52)
NOTES 1. RAK4630-8-SM-I (u.FL/MHF variant): RF pads 15 + 37 are internally disconnected — LoRa antenna via MHF pigtail to bulkhead; no RF routing on this board. 2. 3V3 rail arrives via harness from charger board; Walter power-kill cycles this rail. RTC rides through power-kills on C4 (supercap back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
All four supply pins tied to +3V3 (normal-voltage mode, 2.0–3.6 V). Never feed raw battery here — 3V3 comes from the charger-board LDO.

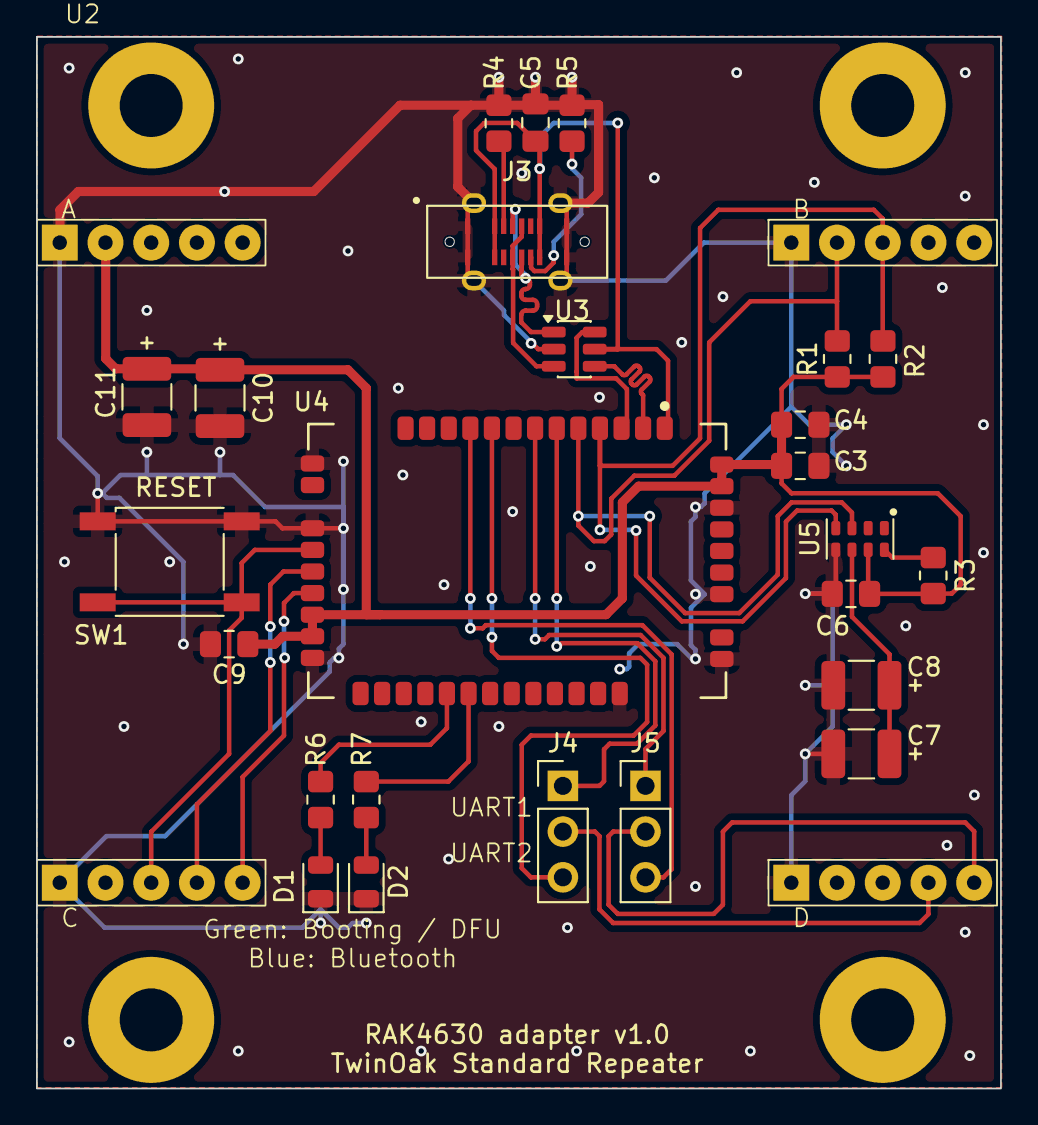
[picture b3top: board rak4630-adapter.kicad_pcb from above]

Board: 2 copper layers, 53.6 x 58.4 mm, 26 parts (0 on the bottom side), 26 nets.

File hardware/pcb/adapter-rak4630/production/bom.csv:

Designator,Footprint,Quantity,Value,LCSC Part #
"C10, C11",CPH3225A,2,100u 6.3V,C49066
"C3, C6, C9",0805,3,100n,C49678
C4,0805,1,10u,C15850
C5,0805,1,4u7,C1779
D1,0805,1,GRN,C2297
D2,0805,1,BLU,C2293
J3,USB_C_Receptacle_XUNPU_TYPEC-303-ACP16_Vertical,1,USB-C,C720628
"R1, R2, R6, R7",0805,4,1k,C17513
R3,0805,1,10k,C17414
"R4, R5",0805,2,5k1,C27834
SW1,SW_Push_Kinghelm_KH-6X6X5H-STM,1,RESET,C2837531
U3,SOT-23-6,1,USBLC6-2SC6,C7519
U4,RAK4630,1,RAK4630-8-SM-I,C32315253
